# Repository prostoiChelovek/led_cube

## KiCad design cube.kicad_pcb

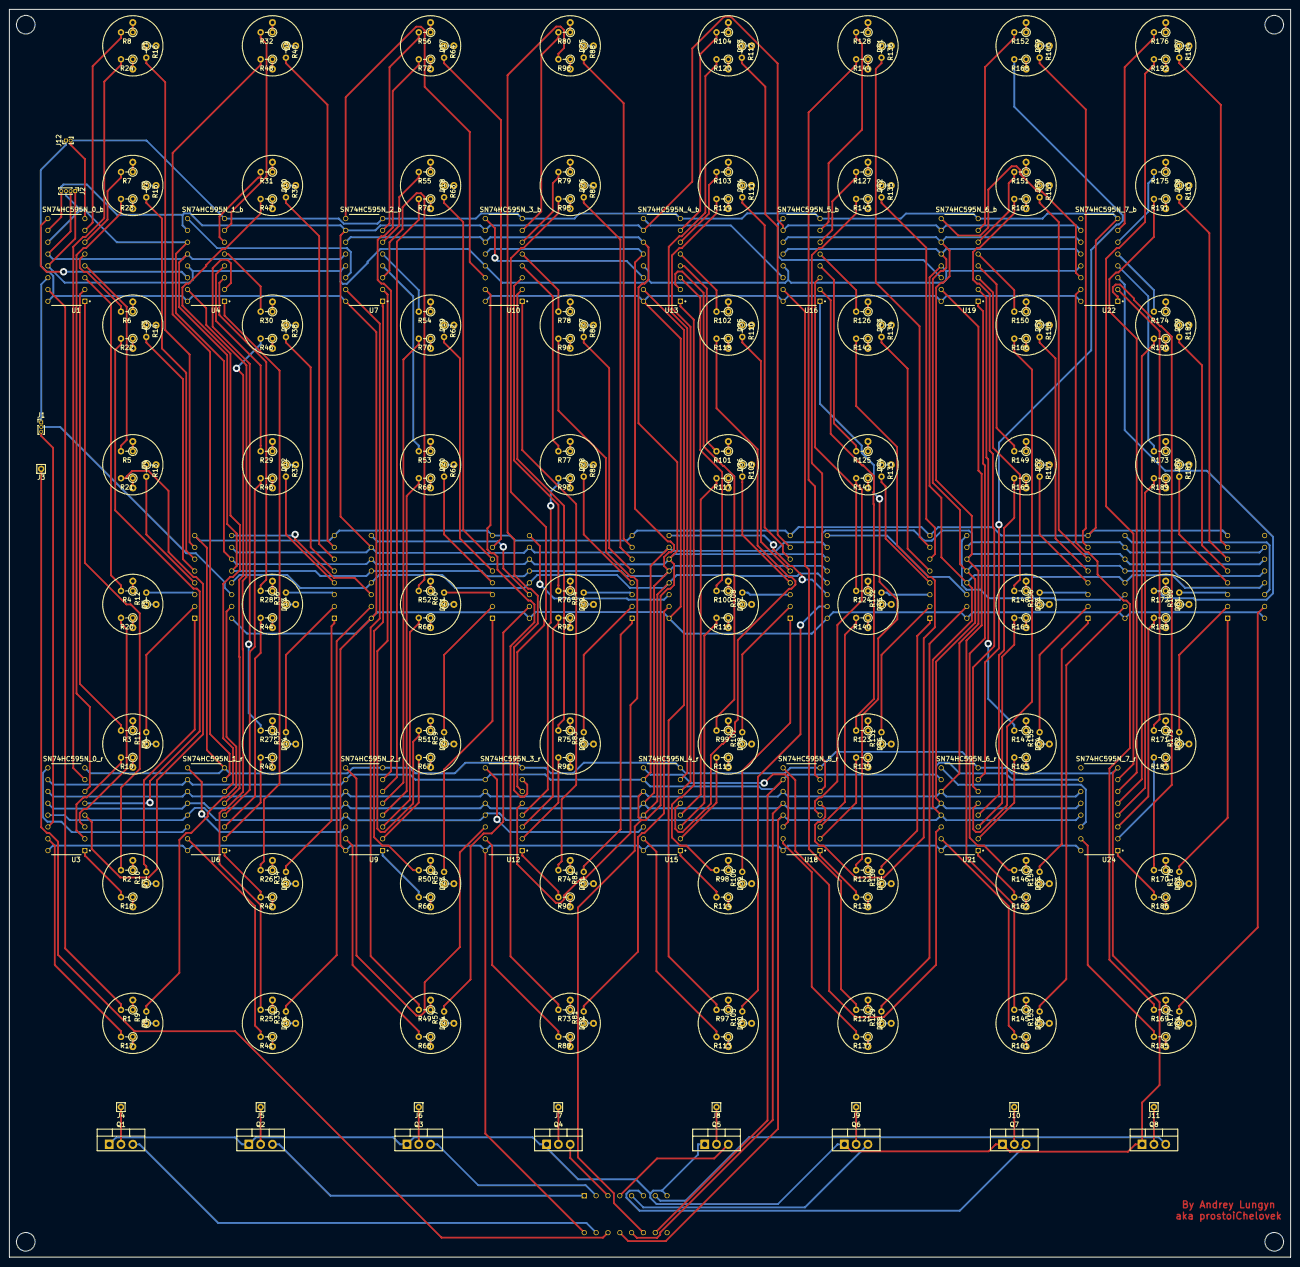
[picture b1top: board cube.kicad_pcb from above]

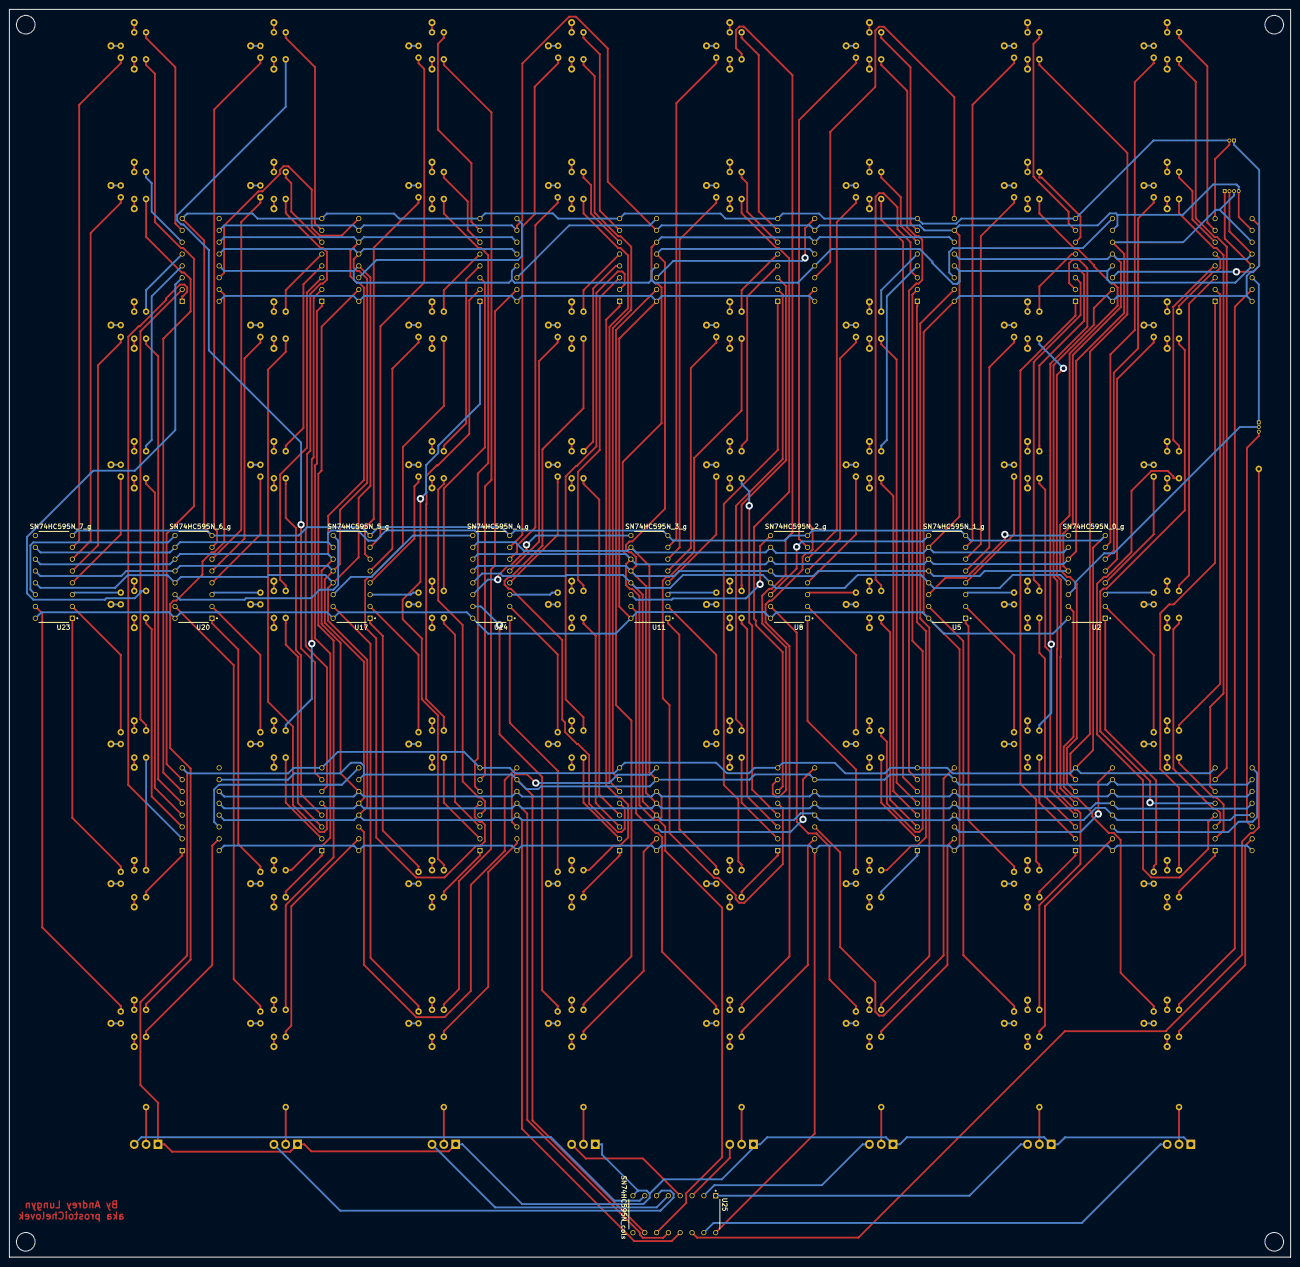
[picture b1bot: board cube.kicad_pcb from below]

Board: 2 copper layers, 275.2 x 268.0 mm, 301 parts (9 on the bottom side), 431 nets.

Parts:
D1: led_0_0; led_pad
D2: led_0_1; led_pad
D3: led_0_2; led_pad
D4: led_0_3; led_pad
D5: led_0_4; led_pad
D6: led_0_5; led_pad
D7: led_0_6; led_pad
D8: led_0_7; led_pad
D9: led_1_0; led_pad
D10: led_1_1; led_pad
D11: led_1_2; led_pad
D12: led_1_3; led_pad
D13: led_1_4; led_pad
D14: led_1_5; led_pad
D15: led_1_6; led_pad
D16: led_1_7; led_pad
D17: led_2_0; led_pad
D18: led_2_1; led_pad
D19: led_2_2; led_pad
D20: led_2_3; led_pad
D21: led_2_4; led_pad
D22: led_2_5; led_pad
D23: led_2_6; led_pad
D24: led_2_7; led_pad
D25: led_3_0; led_pad
D26: led_3_1; led_pad
D27: led_3_2; led_pad
D28: led_3_3; led_pad
D29: led_3_4; led_pad
D30: led_3_5; led_pad
D31: led_3_6; led_pad
D32: led_3_7; led_pad
D33: led_4_0; led_pad
D34: led_4_1; led_pad
D35: led_4_2; led_pad
D36: led_4_3; led_pad
D37: led_4_4; led_pad
D38: led_4_5; led_pad
D39: led_4_6; led_pad
D40: led_4_7; led_pad
D41: led_5_0; led_pad
D42: led_5_1; led_pad
D43: led_5_2; led_pad
D44: led_5_3; led_pad
D45: led_5_4; led_pad
D46: led_5_5; led_pad
D47: led_5_6; led_pad
D48: led_5_7; led_pad
D49: led_6_0; led_pad
D50: led_6_1; led_pad
D51: led_6_2; led_pad
D52: led_6_3; led_pad
D53: led_6_4; led_pad
D54: led_6_5; led_pad
D55: led_6_6; led_pad
D56: led_6_7; led_pad
D57: led_7_0; led_pad
D58: led_7_1; led_pad
D59: led_7_2; led_pad
D60: led_7_3; led_pad
D61: led_7_4; led_pad
D62: led_7_5; led_pad
D63: led_7_6; led_pad
D64: led_7_7; led_pad
J1: serial_conn; PinHeader_1x03_P1.00mm_Vertical
J2: shifters_common_conn; PinHeader_1x04_P1.00mm_Vertical
J3, J4, J5, J6, J7, J8, J9, J10, J11: Conn_01x01; Pin_D0.7mm_L6.5mm_W1.8mm_FlatFork
J12: power_conn; PinHeader_1x02_P1.00mm_Vertical
Q1, Q2, Q3, Q4, Q5, Q6, Q7, Q8: IRF9540N; TO-220-3_Vertical
R1, R2, R3, R4, R5, R6, R7, R8, R9, R10, R11, R12, R13, R14, R15, R16, R17, R18, R19, R20, R21, R22, R23, R24, R25, R26, R27, R28, R29, R30, R31, R32, R33, R34, R35, R36, R37, R38, R39, R40, R41, R42, R43, R44, R45, R46, R47, R48, R49, R50, R51, R52, R53, R54, R55, R56, R57, R58, R59, R60, R61, R62, R63, R64, R65, R66, R67, R68, R69, R70, R71, R72, R73, R74, R75, R76, R77, R78, R79, R80, R81, R82, R83, R84, R85, R86, R87, R88, R89, R90, R91, R92, R93, R94, R95, R96, R97, R98, R99, R100, R101, R102, R103, R104, R105, R106, R107, R108, R109, R110, R111, R112, R113, R114, R115, R116, R117, R118, R119, R120, R121, R122, R123, R124, R125, R126, R127, R128, R129, R130, R131, R132, R133, R134, R135, R136, R137, R138, R139, R140, R141, R142, R143, R144, R145, R146, R147, R148, R149, R150, R151, R152, R153, R154, R155, R156, R157, R158, R159, R160, R161, R162, R163, R164, R165, R166, R167, R168, R169, R170, R171, R172, R173, R174, R175, R176, R177, R178, R179, R180, R181, R182, R183, R184, R185, R186, R187, R188, R189, R190, R191, R192: R; R_Axial_DIN0204_L3.6mm_D1.6mm_P2.54mm_Vertical
U1: SN74HC595N_0_b; DIP794W45P254L1969H508Q16
U2: SN74HC595N_0_g; DIP794W45P254L1969H508Q16
U3: SN74HC595N_0_r; DIP794W45P254L1969H508Q16
U4: SN74HC595N_1_b; DIP794W45P254L1969H508Q16
U5: SN74HC595N_1_g; DIP794W45P254L1969H508Q16
U6: SN74HC595N_1_r; DIP794W45P254L1969H508Q16
U7: SN74HC595N_2_b; DIP794W45P254L1969H508Q16
U8: SN74HC595N_2_g; DIP794W45P254L1969H508Q16
U9: SN74HC595N_2_r; DIP794W45P254L1969H508Q16
U10: SN74HC595N_3_b; DIP794W45P254L1969H508Q16
U11: SN74HC595N_3_g; DIP794W45P254L1969H508Q16
U12: SN74HC595N_3_r; DIP794W45P254L1969H508Q16
U13: SN74HC595N_4_b; DIP794W45P254L1969H508Q16
U14: SN74HC595N_4_g; DIP794W45P254L1969H508Q16
U15: SN74HC595N_4_r; DIP794W45P254L1969H508Q16
U16: SN74HC595N_5_b; DIP794W45P254L1969H508Q16
U17: SN74HC595N_5_g; DIP794W45P254L1969H508Q16
U18: SN74HC595N_5_r; DIP794W45P254L1969H508Q16
U19: SN74HC595N_6_b; DIP794W45P254L1969H508Q16
U20: SN74HC595N_6_g; DIP794W45P254L1969H508Q16
U21: SN74HC595N_6_r; DIP794W45P254L1969H508Q16
U22: SN74HC595N_7_b; DIP794W45P254L1969H508Q16
U23: SN74HC595N_7_g; DIP794W45P254L1969H508Q16
U24: SN74HC595N_7_r; DIP794W45P254L1969H508Q16
U25: SN74HC595N_cols; DIP794W45P254L1969H508Q16

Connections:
+5V: J12.1, U1.16, U2.16, U3.16, U4.16, U5.16, U6.16, U7.16, U8.16, U9.16, U10.16, U11.16, U12.16, U13.16, U14.16, U15.16, U16.16, U17.16, U18.16, U19.16, U20.16, U21.16, U22.16, U23.16, U24.16, U25.16
GND: J12.2, Q1.1, Q2.1, Q3.1, Q4.1, Q5.1, Q6.1, Q7.1, Q8.1, U1.8, U2.8, U3.8, U4.8, U5.8, U6.8, U7.8, U8.8, U9.8, U10.8, U11.8, U12.8, U13.8, U14.8, U15.8, U16.8, U17.8, U18.8, U19.8, U20.8, U21.8, U22.8, U23.8, U24.8, U25.8
unnamed: J4.1, Q1.2
unnamed: J5.1, Q2.2
unnamed: J6.1, Q3.2
unnamed: J7.1, Q4.2
unnamed: J8.1, Q5.2
unnamed: J9.1, Q6.2
unnamed: J10.1, Q7.2
unnamed: J11.1, Q8.2
unnamed: Q1.3, U25.15
unnamed: Q2.3, U25.1
unnamed: Q3.3, U25.2
unnamed: Q4.3, U25.3
unnamed: Q5.3, U25.4
unnamed: Q6.3, U25.5
unnamed: Q7.3, U25.6
unnamed: Q8.3, U25.7
unnamed: R1.2, U1.15
unnamed: R2.2, U1.1
unnamed: R3.2, U1.2
unnamed: R4.2, U1.3
unnamed: R5.2, U1.4
unnamed: R6.2, U1.5
unnamed: R7.2, U1.6
unnamed: R8.2, U1.7
unnamed: R9.2, U2.15
unnamed: R10.2, U2.1
unnamed: R11.2, U2.2
unnamed: R12.2, U2.3
unnamed: R13.2, U2.4
unnamed: R14.2, U2.5
unnamed: R15.2, U2.6
unnamed: R16.2, U2.7
unnamed: R17.2, U3.15
unnamed: R18.2, U3.1
unnamed: R19.2, U3.2
unnamed: R20.2, U3.3
unnamed: R21.2, U3.4
unnamed: R22.2, U3.5
unnamed: R23.2, U3.6
unnamed: R24.2, U3.7
unnamed: R25.2, U4.15
unnamed: R26.2, U4.1
unnamed: R27.2, U4.2
unnamed: R28.2, U4.3
unnamed: R29.2, U4.4
unnamed: R30.2, U4.5
unnamed: R31.2, U4.6
unnamed: R32.2, U4.7
unnamed: R33.2, U5.15
unnamed: R34.2, U5.1
unnamed: R35.2, U5.2
unnamed: R36.2, U5.3
unnamed: R37.2, U5.4
unnamed: R38.2, U5.5
unnamed: R39.2, U5.6
unnamed: R40.2, U5.7
unnamed: R41.2, U6.15
unnamed: R42.2, U6.1
unnamed: R43.2, U6.2
unnamed: R44.2, U6.3
unnamed: R45.2, U6.4
unnamed: R46.2, U6.5
unnamed: R47.2, U6.6
unnamed: R48.2, U6.7
unnamed: R49.2, U7.15
unnamed: R50.2, U7.1
unnamed: R51.2, U7.2
unnamed: R52.2, U7.3
unnamed: R53.2, U7.4
unnamed: R54.2, U7.5
unnamed: R55.2, U7.6
unnamed: R56.2, U7.7
unnamed: R57.2, U8.15
unnamed: R58.2, U8.1
unnamed: R59.2, U8.2
unnamed: R60.2, U8.3
unnamed: R61.2, U8.4
unnamed: R62.2, U8.5
unnamed: R63.2, U8.6
unnamed: R64.2, U8.7
unnamed: R65.2, U9.15
unnamed: R66.2, U9.1
unnamed: R67.2, U9.2
unnamed: R68.2, U9.3
unnamed: R69.2, U9.4
unnamed: R70.2, U9.5
unnamed: R71.2, U9.6
unnamed: R72.2, U9.7
unnamed: R73.2, U10.15
unnamed: R74.2, U10.1
unnamed: R75.2, U10.2
unnamed: R76.2, U10.3
unnamed: R77.2, U10.4
unnamed: R78.2, U10.5
unnamed: R79.2, U10.6
unnamed: R80.2, U10.7
unnamed: R81.2, U11.15
unnamed: R82.2, U11.1
unnamed: R83.2, U11.2
unnamed: R84.2, U11.3
unnamed: R85.2, U11.4
unnamed: R86.2, U11.5
unnamed: R87.2, U11.6
unnamed: R88.2, U11.7
unnamed: R89.2, U12.15
unnamed: R90.2, U12.1
unnamed: R91.2, U12.2
unnamed: R92.2, U12.3
unnamed: R93.2, U12.4
unnamed: R94.2, U12.5
unnamed: R95.2, U12.6
unnamed: R96.2, U12.7
unnamed: R97.2, U13.15
unnamed: R98.2, U13.1
unnamed: R99.2, U13.2
unnamed: R100.2, U13.3
unnamed: R101.2, U13.4
unnamed: R102.2, U13.5
unnamed: R103.2, U13.6
unnamed: R104.2, U13.7
unnamed: R105.2, U14.15
unnamed: R106.2, U14.1
unnamed: R107.2, U14.2
unnamed: R108.2, U14.3
unnamed: R109.2, U14.4
unnamed: R110.2, U14.5
unnamed: R111.2, U14.6
unnamed: R112.2, U14.7
unnamed: R113.2, U15.15
unnamed: R114.2, U15.1
unnamed: R115.2, U15.2
unnamed: R116.2, U15.3
unnamed: R117.2, U15.4
unnamed: R118.2, U15.5
unnamed: R119.2, U15.6
unnamed: R120.2, U15.7
unnamed: R121.2, U16.15
unnamed: R122.2, U16.1
unnamed: R123.2, U16.2
unnamed: R124.2, U16.3
unnamed: R125.2, U16.4
unnamed: R126.2, U16.5
unnamed: R127.2, U16.6
unnamed: R128.2, U16.7
unnamed: R129.2, U17.15
unnamed: R130.2, U17.1
unnamed: R131.2, U17.2
unnamed: R132.2, U17.3
unnamed: R133.2, U17.4
unnamed: R134.2, U17.5
unnamed: R135.2, U17.6
unnamed: R136.2, U17.7
unnamed: R137.2, U18.15
unnamed: R138.2, U18.1
unnamed: R139.2, U18.2
unnamed: R140.2, U18.3
unnamed: R141.2, U18.4
unnamed: R142.2, U18.5
unnamed: R143.2, U18.6
unnamed: R144.2, U18.7
unnamed: R145.2, U19.15
unnamed: R146.2, U19.1
unnamed: R147.2, U19.2
unnamed: R148.2, U19.3
unnamed: R149.2, U19.4
unnamed: R150.2, U19.5
unnamed: R151.2, U19.6
unnamed: R152.2, U19.7
unnamed: R153.2, U20.15
unnamed: R154.2, U20.1
unnamed: R155.2, U20.2
unnamed: R156.2, U20.3
unnamed: R157.2, U20.4
unnamed: R158.2, U20.5
unnamed: R159.2, U20.6
unnamed: R160.2, U20.7
unnamed: R161.2, U21.15
unnamed: R162.2, U21.1
unnamed: R163.2, U21.2
unnamed: R164.2, U21.3
unnamed: R165.2, U21.4
unnamed: R166.2, U21.5
unnamed: R167.2, U21.6
unnamed: R168.2, U21.7
unnamed: R169.2, U22.15
unnamed: R170.2, U22.1
unnamed: R171.2, U22.2
unnamed: R172.2, U22.3
unnamed: R173.2, U22.4
unnamed: R174.2, U22.5
unnamed: R175.2, U22.6
unnamed: R176.2, U22.7
unnamed: R177.2, U23.15
unnamed: R178.2, U23.1
unnamed: R179.2, U23.2
unnamed: R180.2, U23.3
unnamed: R181.2, U23.4
unnamed: R182.2, U23.5
unnamed: R183.2, U23.6
unnamed: R184.2, U23.7
unnamed: R185.2, U24.15
unnamed: R186.2, U24.1
unnamed: R187.2, U24.2
unnamed: R188.2, U24.3
unnamed: R189.2, U24.4
unnamed: R190.2, U24.5
unnamed: R191.2, U24.6
unnamed: R192.2, U24.7
clock: J2.3, U1.11, U2.11, U3.11, U4.11, U5.11, U6.11, U7.11, U8.11, U9.11, U10.11, U11.11, U12.11, U13.11, U14.11, U15.11, U16.11, U17.11, U18.11, U19.11, U20.11, U21.11, U22.11, U23.11, U24.11, U25.11
enable: J2.1, U1.13, U2.13, U3.13, U4.13, U5.13, U6.13, U7.13, U8.13, U9.13, U10.13, U11.13, U12.13, U13.13, U14.13, U15.13, U16.13, U17.13, U18.13, U19.13, U20.13, U21.13, U22.13, U23.13, U24.13, U25.13
latch: J2.2, U1.12, U2.12, U3.12, U4.12, U5.12, U6.12, U7.12, U8.12, U9.12, U10.12, U11.12, U12.12, U13.12, U14.12, U15.12, U16.12, U17.12, U18.12, U19.12, U20.12, U21.12, U22.12, U23.12, U24.12, U25.12
led_0_0_b: D1.3, R8.1
led_0_0_g: D1.2, R16.1
led_0_0_r: D1.1, R24.1
led_0_1_b: D2.3, R7.1
led_0_1_g: D2.2, R15.1
led_0_1_r: D2.1, R23.1
led_0_2_b: D3.3, R6.1
led_0_2_g: D3.2, R14.1
led_0_2_r: D3.1, R22.1
led_0_3_b: D4.3, R5.1
led_0_3_g: D4.2, R13.1
led_0_3_r: D4.1, R21.1
led_0_4_b: D5.3, R4.1
led_0_4_g: D5.2, R12.1
led_0_4_r: D5.1, R20.1
led_0_5_b: D6.3, R3.1
led_0_5_g: D6.2, R11.1
led_0_5_r: D6.1, R19.1
led_0_6_b: D7.3, R2.1
led_0_6_g: D7.2, R10.1
led_0_6_r: D7.1, R18.1
led_0_7_b: D8.3, R1.1
led_0_7_g: D8.2, R9.1
led_0_7_r: D8.1, R17.1
led_1_0_b: D9.3, R32.1
led_1_0_g: D9.2, R40.1
led_1_0_r: D9.1, R48.1
led_1_1_b: D10.3, R31.1
led_1_1_g: D10.2, R39.1
led_1_1_r: D10.1, R47.1
led_1_2_b: D11.3, R30.1
led_1_2_g: D11.2, R38.1
led_1_2_r: D11.1, R46.1
led_1_3_b: D12.3, R29.1
led_1_3_g: D12.2, R37.1
led_1_3_r: D12.1, R45.1
led_1_4_b: D13.3, R28.1
led_1_4_g: D13.2, R36.1
led_1_4_r: D13.1, R44.1
led_1_5_b: D14.3, R27.1
led_1_5_g: D14.2, R35.1
led_1_5_r: D14.1, R43.1
led_1_6_b: D15.3, R26.1
led_1_6_g: D15.2, R34.1
led_1_6_r: D15.1, R42.1
led_1_7_b: D16.3, R25.1
led_1_7_g: D16.2, R33.1
led_1_7_r: D16.1, R41.1
led_2_0_b: D17.3, R56.1
led_2_0_g: D17.2, R64.1
led_2_0_r: D17.1, R72.1
led_2_1_b: D18.3, R55.1
led_2_1_g: D18.2, R63.1
led_2_1_r: D18.1, R71.1
led_2_2_b: D19.3, R54.1
led_2_2_g: D19.2, R62.1
led_2_2_r: D19.1, R70.1
led_2_3_b: D20.3, R53.1
led_2_3_g: D20.2, R61.1
led_2_3_r: D20.1, R69.1
led_2_4_b: D21.3, R52.1
led_2_4_g: D21.2, R60.1
led_2_4_r: D21.1, R68.1
led_2_5_b: D22.3, R51.1
led_2_5_g: D22.2, R59.1
led_2_5_r: D22.1, R67.1
led_2_6_b: D23.3, R50.1
led_2_6_g: D23.2, R58.1
led_2_6_r: D23.1, R66.1
led_2_7_b: D24.3, R49.1
led_2_7_g: D24.2, R57.1
led_2_7_r: D24.1, R65.1
led_3_0_b: D25.3, R80.1
led_3_0_g: D25.2, R88.1
led_3_0_r: D25.1, R96.1
led_3_1_b: D26.3, R79.1
led_3_1_g: D26.2, R87.1
led_3_1_r: D26.1, R95.1
led_3_2_b: D27.3, R78.1
led_3_2_g: D27.2, R86.1
led_3_2_r: D27.1, R94.1
led_3_3_b: D28.3, R77.1
led_3_3_g: D28.2, R85.1
led_3_3_r: D28.1, R93.1
led_3_4_b: D29.3, R76.1
led_3_4_g: D29.2, R84.1
led_3_4_r: D29.1, R92.1
led_3_5_b: D30.3, R75.1
led_3_5_g: D30.2, R83.1
led_3_5_r: D30.1, R91.1
led_3_6_b: D31.3, R74.1
led_3_6_g: D31.2, R82.1
led_3_6_r: D31.1, R90.1
led_3_7_b: D32.3, R73.1
led_3_7_g: D32.2, R81.1
led_3_7_r: D32.1, R89.1
led_4_0_b: D33.3, R104.1
led_4_0_g: D33.2, R112.1
led_4_0_r: D33.1, R120.1
led_4_1_b: D34.3, R103.1
led_4_1_g: D34.2, R111.1
led_4_1_r: D34.1, R119.1
led_4_2_b: D35.3, R102.1
led_4_2_g: D35.2, R110.1
led_4_2_r: D35.1, R118.1
led_4_3_b: D36.3, R101.1
led_4_3_g: D36.2, R109.1
led_4_3_r: D36.1, R117.1
led_4_4_b: D37.3, R100.1
led_4_4_g: D37.2, R108.1
led_4_4_r: D37.1, R116.1
led_4_5_b: D38.3, R99.1
led_4_5_g: D38.2, R107.1
led_4_5_r: D38.1, R115.1
led_4_6_b: D39.3, R98.1
led_4_6_g: D39.2, R106.1
led_4_6_r: D39.1, R114.1
led_4_7_b: D40.3, R97.1
led_4_7_g: D40.2, R105.1
led_4_7_r: D40.1, R113.1
led_5_0_b: D41.3, R128.1
led_5_0_g: D41.2, R136.1
led_5_0_r: D41.1, R144.1
led_5_1_b: D42.3, R127.1
led_5_1_g: D42.2, R135.1
led_5_1_r: D42.1, R143.1
led_5_2_b: D43.3, R126.1
led_5_2_g: D43.2, R134.1
led_5_2_r: D43.1, R142.1
led_5_3_b: D44.3, R125.1
led_5_3_g: D44.2, R133.1
led_5_3_r: D44.1, R141.1
led_5_4_b: D45.3, R124.1
led_5_4_g: D45.2, R132.1
led_5_4_r: D45.1, R140.1
led_5_5_b: D46.3, R123.1
led_5_5_g: D46.2, R131.1
led_5_5_r: D46.1, R139.1
led_5_6_b: D47.3, R122.1
led_5_6_g: D47.2, R130.1
led_5_6_r: D47.1, R138.1
led_5_7_b: D48.3, R121.1
led_5_7_g: D48.2, R129.1
led_5_7_r: D48.1, R137.1
led_6_0_b: D49.3, R152.1
led_6_0_g: D49.2, R160.1
led_6_0_r: D49.1, R168.1
led_6_1_b: D50.3, R151.1
led_6_1_g: D50.2, R159.1
led_6_1_r: D50.1, R167.1
led_6_2_b: D51.3, R150.1
led_6_2_g: D51.2, R158.1
led_6_2_r: D51.1, R166.1
led_6_3_b: D52.3, R149.1
led_6_3_g: D52.2, R157.1
led_6_3_r: D52.1, R165.1
led_6_4_b: D53.3, R148.1
led_6_4_g: D53.2, R156.1
led_6_4_r: D53.1, R164.1
led_6_5_b: D54.3, R147.1
led_6_5_g: D54.2, R155.1
led_6_5_r: D54.1, R163.1
led_6_6_b: D55.3, R146.1
led_6_6_g: D55.2, R154.1
led_6_6_r: D55.1, R162.1
led_6_7_b: D56.3, R145.1
led_6_7_g: D56.2, R153.1
led_6_7_r: D56.1, R161.1
led_7_0_b: D57.3, R176.1
led_7_0_g: D57.2, R184.1
led_7_0_r: D57.1, R192.1
led_7_1_b: D58.3, R175.1
led_7_1_g: D58.2, R183.1
led_7_1_r: D58.1, R191.1
led_7_2_b: D59.3, R174.1
led_7_2_g: D59.2, R182.1
led_7_2_r: D59.1, R190.1
led_7_3_b: D60.3, R173.1
led_7_3_g: D60.2, R181.1
led_7_3_r: D60.1, R189.1
led_7_4_b: D61.3, R172.1
led_7_4_g: D61.2, R180.1
led_7_4_r: D61.1, R188.1
led_7_5_b: D62.3, R171.1
led_7_5_g: D62.2, R179.1
led_7_5_r: D62.1, R187.1
led_7_6_b: D63.3, R170.1
led_7_6_g: D63.2, R178.1
led_7_6_r: D63.1, R186.1
led_7_7_b: D64.3, R169.1
led_7_7_g: D64.2, R177.1
led_7_7_r: D64.1, R185.1
reset: J2.4, U1.10, U2.10, U3.10, U4.10, U5.10, U6.10, U7.10, U8.10, U9.10, U10.10, U11.10, U12.10, U13.10, U14.10, U15.10, U16.10, U17.10, U18.10, U19.10, U20.10, U21.10, U22.10, U23.10, U24.10, U25.10
ser_cols: J3.1, U25.14
ser_first_b: J1.1, U1.14
ser_first_g: J1.2, U2.14
ser_first_r: J1.3, U3.14
ser_out_0_b: U1.9, U4.14
ser_out_0_g: U2.9, U5.14
ser_out_0_r: U3.9, U6.14
ser_out_1_b: U4.9, U7.14
ser_out_1_g: U5.9, U8.14
ser_out_1_r: U6.9, U9.14
ser_out_2_b: U7.9, U10.14
ser_out_2_g: U8.9, U11.14
ser_out_2_r: U9.9, U12.14
ser_out_3_b: U10.9, U13.14
ser_out_3_g: U11.9, U14.14
ser_out_3_r: U12.9, U15.14
ser_out_4_b: U13.9, U16.14
ser_out_4_g: U14.9, U17.14
ser_out_4_r: U15.9, U18.14
ser_out_5_b: U16.9, U19.14
ser_out_5_g: U17.9, U20.14
ser_out_5_r: U18.9, U21.14
ser_out_6_b: U19.9, U22.14
ser_out_6_g: U20.9, U23.14
ser_out_6_r: U21.9, U24.14

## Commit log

2020-09-20 replace led pads on 1st row, fix its red conns
2020-09-20 fix 1s rows's blue conns
2020-09-20 fix 1s rows's green conns
2020-09-20 fix 2nd rows's red conns
2020-09-20 fix 2nd rows's blue conns
2020-09-20 fix 2nd rows's green conns
2020-09-20 fix 3rd rows's red conns
2020-09-20 fix 3rd rows's blue conns
2020-09-20 fix 3rd rows's green conns
2020-09-20 fix 4th rows's red conns
2020-09-20 fix 4th rows's blue conns
2020-09-20 fix 4th rows's green conns
2020-09-20 fix 5th rows's red conns
2020-09-20 fix 5th rows's blue conns
2020-09-20 fix 5th rows's green conns
2020-09-20 fix 6th rows's red conns
2020-09-20 fix 6th rows's blue conns
2020-09-20 fix 6th rows's green conns
2020-09-20 fix 7th rows's red conns
2020-09-20 fix 7th rows's blue conns
2020-09-20 fix 7th rows's green conns
2020-09-20 fix 8th rows's red conns
2020-09-20 fix 8th rows's blue conns
2020-09-20 fix 8th rows's green conns
2020-09-20 layout col switcher
2020-09-20 connect power and fix unconnected
2020-09-20 add copytight and fix some tracks
2020-11-04 add mounting holes and fix edge cuts' alignment
2020-11-09 make tracks thicker on the 1st row
2020-11-11 make all tracks thicker and fix some clearances at the bottom
2020-11-14 fix clearances on the 2nd row
2020-11-14 fix clearances for 2nd row's greens and fix messed up 2b's tracks
2020-11-15 redo routing using the FreeRouting autorouter
2020-11-15 move power connector and increase vias' cost
2020-11-15 increase vias' diameters and tweak some other parameters
2020-11-15 tweak a pcb a tiny little bit
2020-11-15 add pcb pdf files for printing
